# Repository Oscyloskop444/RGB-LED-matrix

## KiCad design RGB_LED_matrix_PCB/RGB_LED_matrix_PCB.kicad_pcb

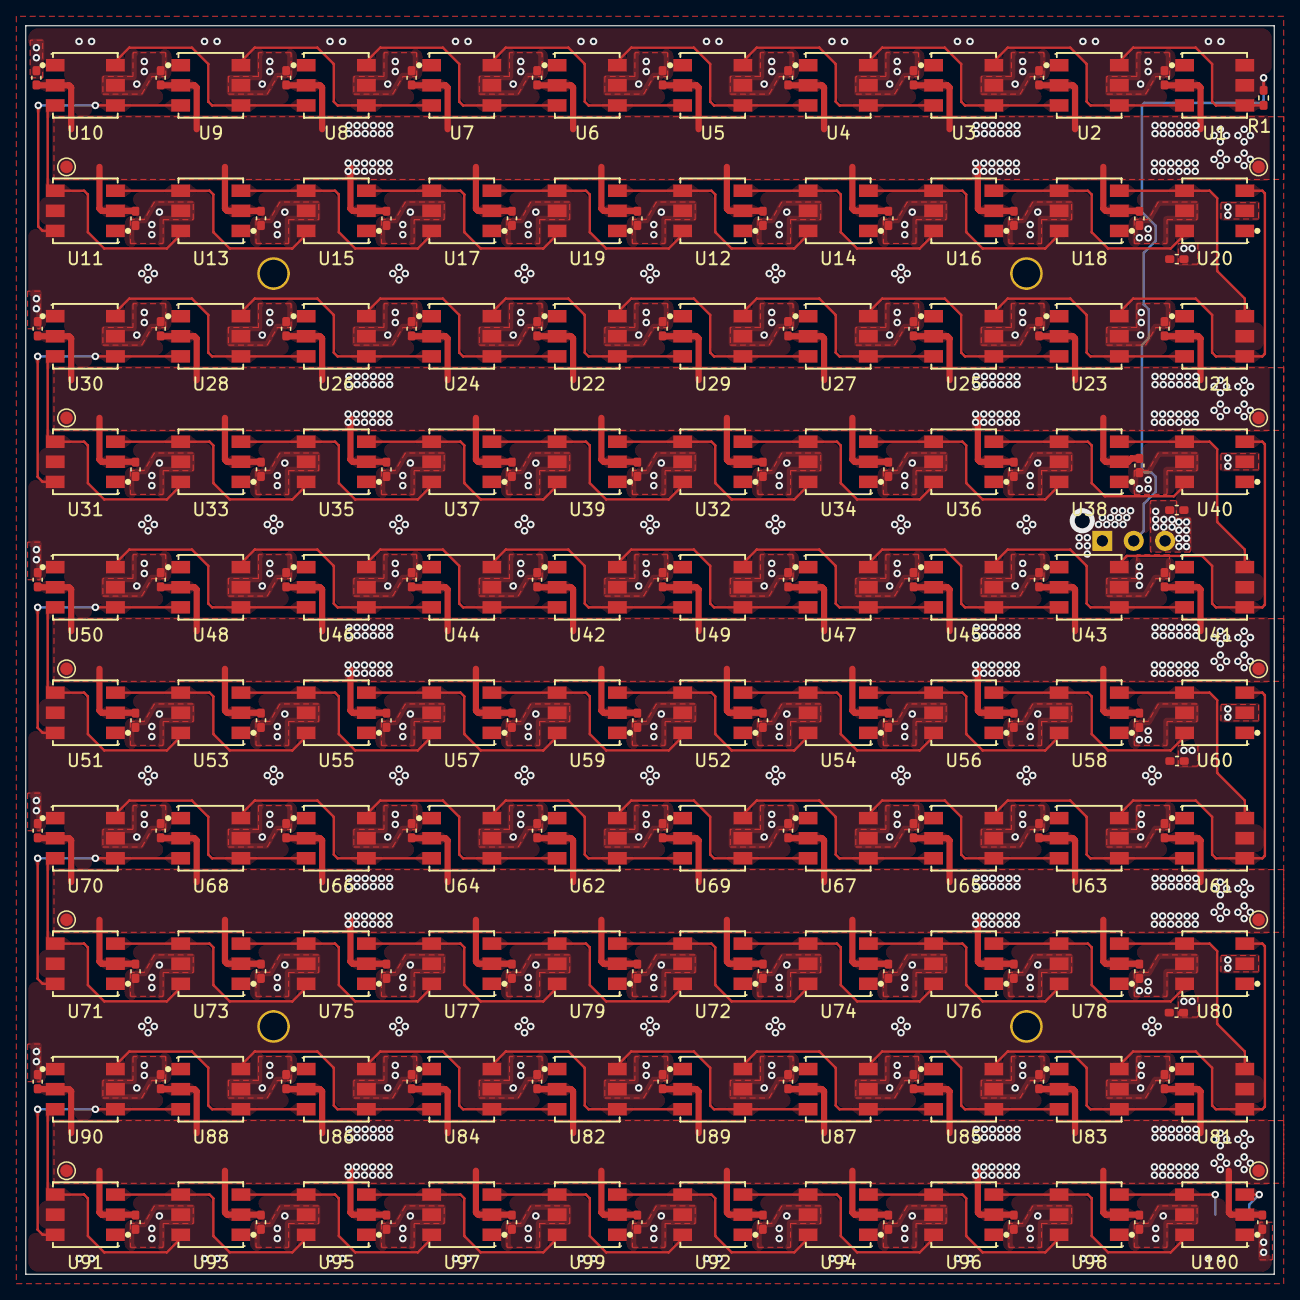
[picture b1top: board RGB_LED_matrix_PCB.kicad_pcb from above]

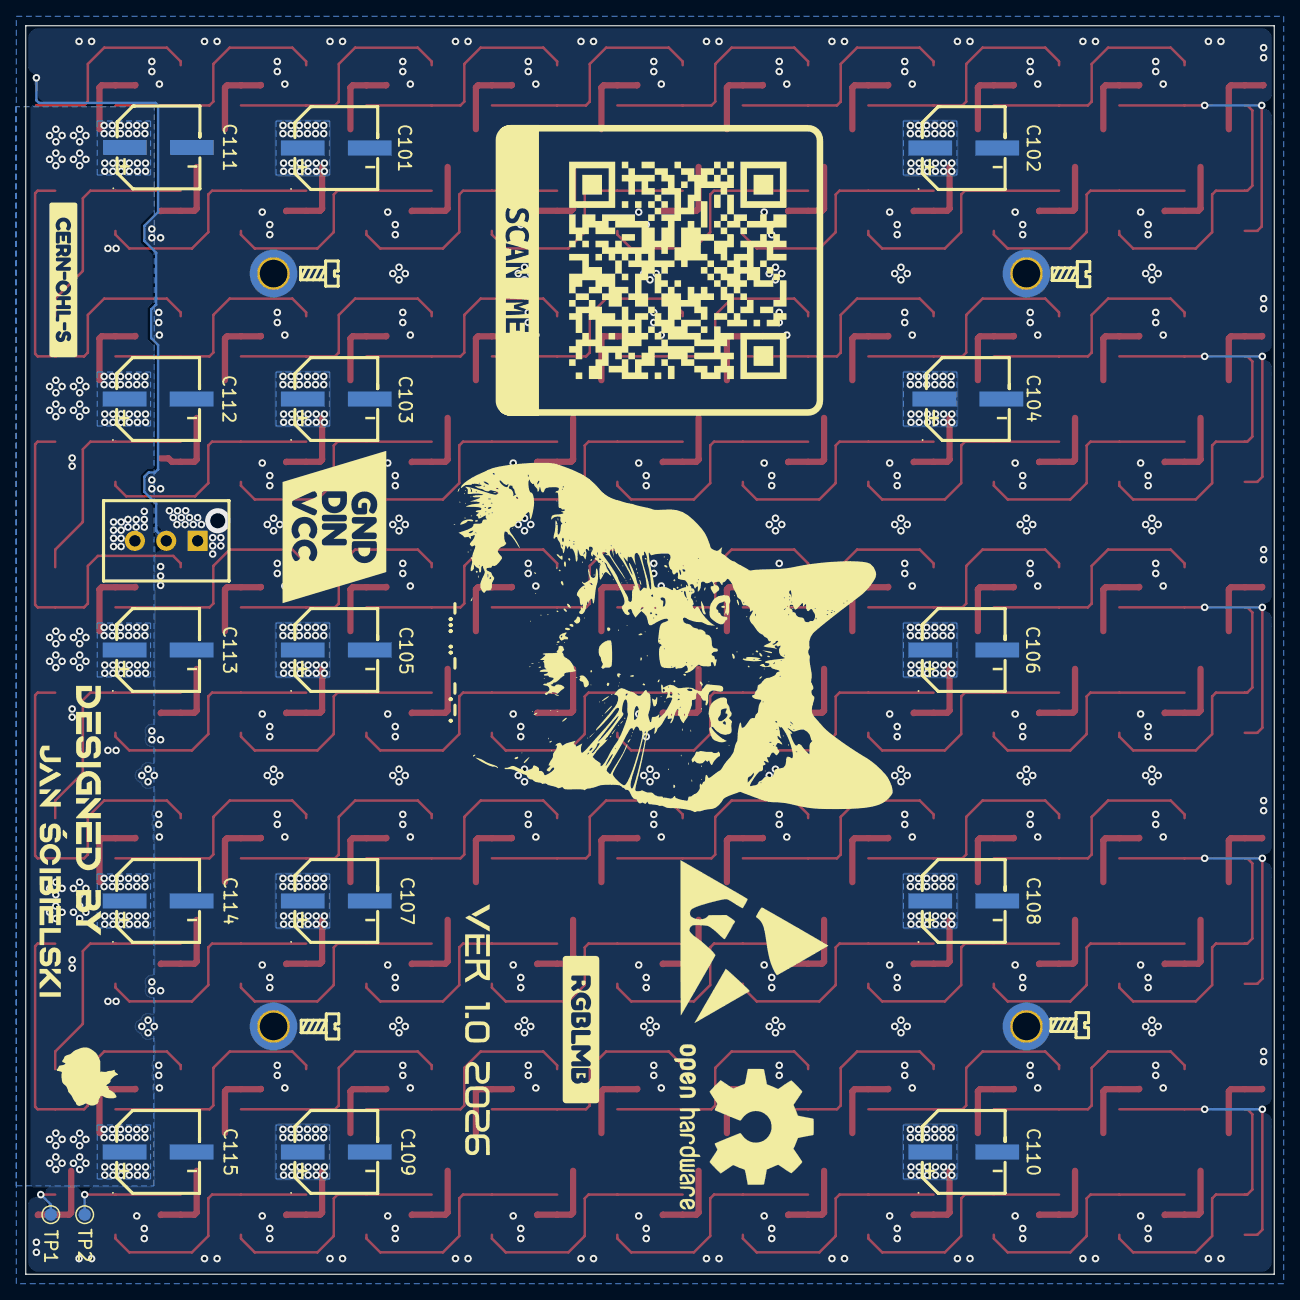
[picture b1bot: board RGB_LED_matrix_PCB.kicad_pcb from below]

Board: 2 copper layers, 99.5 x 99.5 mm, 237 parts (26 on the bottom side), 104 nets.

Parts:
C1, C2, C3, C4, C5, C6, C7, C8, C9, C10, C11, C12, C13, C14, C15, C16, C17, C18, C19, C20, C21, C22, C23, C24, C25, C26, C27, C28, C29, C30, C31, C32, C33, C34, C35, C36, C37, C38, C39, C40, C41, C42, C43, C44, C45, C46, C47, C48, C49, C50, C51, C52, C53, C54, C55, C56, C57, C58, C59, C60, C61, C62, C63, C64, C65, C66, C67, C68, C69, C70, C71, C72, C73, C74, C75, C76, C77, C78, C79, C80, C81, C82, C83, C84, C85, C86, C87, C88, C89, C90, C91, C92, C93, C94, C95, C96, C97, C98, C99, C100: 100nF; C_0402_1005Metric_Pad0.74x0.62mm_HandSolder
C101, C102, C103, C104, C105, C106, C107, C108, C109, C110, C111, C112, C113, C114, C115: 100uF; C19673858_CAP-SMD_BD6_3-L6_5-W6_5-LS7_2-FD_1
CN1: B03B-XASK-1-A(LF)(SN); C264992_CONN-TH_B03B-XASK-1-A-LF-SN
H1, H2, H3, H4: MountingHole_Pad; MountingHole_2.2mm_M2_DIN965_Pad_TopOnly
R1: 470R; R_0402_1005Metric_Pad0.72x0.64mm_HandSolder
TP1: DOUT; TestPoint_Pad_D1.0mm
TP2: DOUT_B; TestPoint_Pad_D1.0mm
TP3, TP4, TP5, TP6, TP7, TP8, TP9, TP10, TP11, TP12: +12V; TestPoint_Pad_D1.0mm
U1, U2, U3, U4, U5, U6, U7, U8, U9, U10, U11, U12, U13, U14, U15, U16, U17, U18, U19, U20, U21, U22, U23, U24, U25, U26, U27, U28, U29, U30, U31, U32, U33, U34, U35, U36, U37, U38, U39, U40, U41, U42, U43, U44, U45, U46, U47, U48, U49, U50, U51, U52, U53, U54, U55, U56, U57, U58, U59, U60, U61, U62, U63, U64, U65, U66, U67, U68, U69, U70, U71, U72, U73, U74, U75, U76, U77, U78, U79, U80, U81, U82, U83, U84, U85, U86, U87, U88, U89, U90, U91, U92, U93, U94, U95, U96, U97, U98, U99, U100: WS2815F; C22371533_LED-SMD_6P-L5_0-W5_0-TL
kibuzzard-6AA54A1E: G***; kibuzzard-6AA54A1E
kobee-studio-6AA9F6C4: Kobee Studio; kobee-studio-6AA9F6C4
kobee-studio-6AA9F9DB: Kobee Studio; kobee-studio-6AA9F9DB
kobee-studio-6AA92370: Kobee Studio; kobee-studio-6AA92370

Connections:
+12V: C1.2, C2.2, C3.2, C4.2, C5.2, C6.2, C7.2, C8.2, C9.2, C10.2, C11.2, C12.2, C13.2, C14.2, C15.2, C16.2, C17.2, C18.2, C19.2, C20.2, C21.2, C22.2, C23.2, C24.2, C25.2, C26.2, C27.2, C28.2, C29.2, C30.2, C31.2, C32.2, C33.2, C34.2, C35.2, C36.2, C37.2, C38.2, C39.2, C40.2, C41.2, C42.2, C43.2, C44.2, C45.2, C46.2, C47.2, C48.2, C49.2, C50.2, C51.2, C52.2, C53.2, C54.2, C55.2, C56.2, C57.2, C58.2, C59.2, C60.2, C61.2, C62.2, C63.2, C64.2, C65.2, C66.2, C67.2, C68.2, C69.2, C70.2, C71.2, C72.2, C73.2, C74.2, C75.2, C76.2, C77.2, C78.2, C79.2, C80.2, C81.2, C82.2, C83.2, C84.2, C85.2, C86.2, C87.2, C88.2, C89.2, C90.2, C91.2, C92.2, C93.2, C94.2, C95.2, C96.2, C97.2, C98.2, C99.2, C100.2, C101.1, C102.1, C103.1, C104.1, C105.1, C106.1, C107.1, C108.1, C109.1, C110.1, C111.1, C112.1, C113.1, C114.1, C115.1, CN1.3, TP3.1 (1_1), TP4.1 (1_1), TP5.1 (1_1), TP6.1 (1_1), TP7.1 (1_1), TP8.1 (1_1), TP9.1 (1_1), TP10.1 (1_1), TP11.1 (1_1), TP12.1 (1_1), U1.2 (VDD), U2.2 (VDD), U3.2 (VDD), U4.2 (VDD), U5.2 (VDD), U6.2 (VDD), U7.2 (VDD), U8.2 (VDD), U9.2 (VDD), U10.2 (VDD), U11.2 (VDD), U12.2 (VDD), U13.2 (VDD), U14.2 (VDD), U15.2 (VDD), U16.2 (VDD), U17.2 (VDD), U18.2 (VDD), U19.2 (VDD), U20.2 (VDD), U21.2 (VDD), U22.2 (VDD), U23.2 (VDD), U24.2 (VDD), U25.2 (VDD), U26.2 (VDD), U27.2 (VDD), U28.2 (VDD), U29.2 (VDD), U30.2 (VDD), U31.2 (VDD), U32.2 (VDD), U33.2 (VDD), U34.2 (VDD), U35.2 (VDD), U36.2 (VDD), U37.2 (VDD), U38.2 (VDD), U39.2 (VDD), U40.2 (VDD), U41.2 (VDD), U42.2 (VDD), U43.2 (VDD), U44.2 (VDD), U45.2 (VDD), U46.2 (VDD), U47.2 (VDD), U48.2 (VDD), U49.2 (VDD), U50.2 (VDD), U51.2 (VDD), U52.2 (VDD), U53.2 (VDD), U54.2 (VDD), U55.2 (VDD), U56.2 (VDD), U57.2 (VDD), U58.2 (VDD), U59.2 (VDD), U60.2 (VDD), U61.2 (VDD), U62.2 (VDD), U63.2 (VDD), U64.2 (VDD), U65.2 (VDD), U66.2 (VDD), U67.2 (VDD), U68.2 (VDD), U69.2 (VDD), U70.2 (VDD), U71.2 (VDD), U72.2 (VDD), U73.2 (VDD), U74.2 (VDD), U75.2 (VDD), U76.2 (VDD), U77.2 (VDD), U78.2 (VDD), U79.2 (VDD), U80.2 (VDD), U81.2 (VDD), U82.2 (VDD), U83.2 (VDD), U84.2 (VDD), U85.2 (VDD), U86.2 (VDD), U87.2 (VDD), U88.2 (VDD), U89.2 (VDD), U90.2 (VDD), U91.2 (VDD), U92.2 (VDD), U93.2 (VDD), U94.2 (VDD), U95.2 (VDD), U96.2 (VDD), U97.2 (VDD), U98.2 (VDD), U99.2 (VDD), U100.2 (VDD)
/LED_ROW1/DOUT1: U20.3 (DO), U21.4 (DIN1), U23.6 (DIN2)
/LED_ROW1/DOUT2: U18.3 (DO), U20.4 (DIN1), U21.6 (DIN2)
/LED_ROW2/DOUT1: U30.3 (DO), U31.4 (DIN1), U33.6 (DIN2)
/LED_ROW2/DOUT2: U28.3 (DO), U30.4 (DIN1), U31.6 (DIN2)
/LED_ROW3/DOUT1: U40.3 (DO), U41.4 (DIN1), U43.6 (DIN2)
/LED_ROW3/DOUT2: U38.3 (DO), U40.4 (DIN1), U41.6 (DIN2)
/LED_ROW4/DOUT1: U50.3 (DO), U51.4 (DIN1), U53.6 (DIN2)
/LED_ROW4/DOUT2: U48.3 (DO), U50.4 (DIN1), U51.6 (DIN2)
/LED_ROW5/DOUT1: U60.3 (DO), U61.4 (DIN1), U63.6 (DIN2)
/LED_ROW5/DOUT2: U58.3 (DO), U60.4 (DIN1), U61.6 (DIN2)
/LED_ROW6/DOUT1: U70.3 (DO), U71.4 (DIN1), U73.6 (DIN2)
/LED_ROW6/DOUT2: U68.3 (DO), U70.4 (DIN1), U71.6 (DIN2)
/LED_ROW7/DOUT1: U80.3 (DO), U81.4 (DIN1), U83.6 (DIN2)
/LED_ROW7/DOUT2: U78.3 (DO), U80.4 (DIN1), U81.6 (DIN2)
/LED_ROW8/DOUT1: U90.3 (DO), U91.4 (DIN1), U93.6 (DIN2)
/LED_ROW8/DOUT2: U88.3 (DO), U90.4 (DIN1), U91.6 (DIN2)
/LED_ROW9/DOUT1: TP1.1 (1_1), U100.3 (DO)
/LED_ROW9/DOUT2: TP2.1 (1_1), U98.3 (DO), U100.4 (DIN1)
/LED_ROW/DIN1: R1.1, U1.4 (DIN1), U2.6 (DIN2)
/LED_ROW/DOUT1: U10.3 (DO), U11.4 (DIN1), U13.6 (DIN2)
/LED_ROW/DOUT2: U9.3 (DO), U10.4 (DIN1), U11.6 (DIN2)
GND: C1.1, C2.1, C3.1, C4.1, C5.1, C6.1, C7.1, C8.1, C9.1, C10.1, C11.1, C12.1, C13.1, C14.1, C15.1, C16.1, C17.1, C18.1, C19.1, C20.1, C21.1, C22.1, C23.1, C24.1, C25.1, C26.1, C27.1, C28.1, C29.1, C30.1, C31.1, C32.1, C33.1, C34.1, C35.1, C36.1, C37.1, C38.1, C39.1, C40.1, C41.1, C42.1, C43.1, C44.1, C45.1, C46.1, C47.1, C48.1, C49.1, C50.1, C51.1, C52.1, C53.1, C54.1, C55.1, C56.1, C57.1, C58.1, C59.1, C60.1, C61.1, C62.1, C63.1, C64.1, C65.1, C66.1, C67.1, C68.1, C69.1, C70.1, C71.1, C72.1, C73.1, C74.1, C75.1, C76.1, C77.1, C78.1, C79.1, C80.1, C81.1, C82.1, C83.1, C84.1, C85.1, C86.1, C87.1, C88.1, C89.1, C90.1, C91.1, C92.1, C93.1, C94.1, C95.1, C96.1, C97.1, C98.1, C99.1, C100.1, C101.2, C102.2, C103.2, C104.2, C105.2, C106.2, C107.2, C108.2, C109.2, C110.2, C111.2, C112.2, C113.2, C114.2, C115.2, CN1.1, H1.1 (1_1), H2.1 (1_1), H3.1 (1_1), H4.1 (1_1), U1.5 (GND), U1.6 (DIN2), U2.5 (GND), U3.5 (GND), U4.5 (GND), U5.5 (GND), U6.5 (GND), U7.5 (GND), U8.5 (GND), U9.5 (GND), U10.5 (GND), U11.5 (GND), U12.5 (GND), U13.5 (GND), U14.5 (GND), U15.5 (GND), U16.5 (GND), U17.5 (GND), U18.5 (GND), U19.5 (GND), U20.5 (GND), U21.5 (GND), U22.5 (GND), U23.5 (GND), U24.5 (GND), U25.5 (GND), U26.5 (GND), U27.5 (GND), U28.5 (GND), U29.5 (GND), U30.5 (GND), U31.5 (GND), U32.5 (GND), U33.5 (GND), U34.5 (GND), U35.5 (GND), U36.5 (GND), U37.5 (GND), U38.5 (GND), U39.5 (GND), U40.5 (GND), U41.5 (GND), U42.5 (GND), U43.5 (GND), U44.5 (GND), U45.5 (GND), U46.5 (GND), U47.5 (GND), U48.5 (GND), U49.5 (GND), U50.5 (GND), U51.5 (GND), U52.5 (GND), U53.5 (GND), U54.5 (GND), U55.5 (GND), U56.5 (GND), U57.5 (GND), U58.5 (GND), U59.5 (GND), U60.5 (GND), U61.5 (GND), U62.5 (GND), U63.5 (GND), U64.5 (GND), U65.5 (GND), U66.5 (GND), U67.5 (GND), U68.5 (GND), U69.5 (GND), U70.5 (GND), U71.5 (GND), U72.5 (GND), U73.5 (GND), U74.5 (GND), U75.5 (GND), U76.5 (GND), U77.5 (GND), U78.5 (GND), U79.5 (GND), U80.5 (GND), U81.5 (GND), U82.5 (GND), U83.5 (GND), U84.5 (GND), U85.5 (GND), U86.5 (GND), U87.5 (GND), U88.5 (GND), U89.5 (GND), U90.5 (GND), U91.5 (GND), U92.5 (GND), U93.5 (GND), U94.5 (GND), U95.5 (GND), U96.5 (GND), U97.5 (GND), U98.5 (GND), U99.5 (GND), U100.5 (GND)
unnamed: CN1.2, R1.2
unnamed: U1.3 (DO), U2.4 (DIN1), U3.6 (DIN2)
unnamed: U2.3 (DO), U3.4 (DIN1), U4.6 (DIN2)
unnamed: U3.3 (DO), U4.4 (DIN1), U5.6 (DIN2)
unnamed: U4.3 (DO), U5.4 (DIN1), U6.6 (DIN2)
unnamed: U5.3 (DO), U6.4 (DIN1), U7.6 (DIN2)
unnamed: U6.3 (DO), U7.4 (DIN1), U8.6 (DIN2)
unnamed: U7.3 (DO), U8.4 (DIN1), U9.6 (DIN2)
unnamed: U8.3 (DO), U9.4 (DIN1), U10.6 (DIN2)
unnamed: U11.3 (DO), U13.4 (DIN1), U15.6 (DIN2)
unnamed: U12.4 (DIN1), U14.6 (DIN2), U19.3 (DO)
unnamed: U12.6 (DIN2), U17.3 (DO), U19.4 (DIN1)
unnamed: U12.3 (DO), U14.4 (DIN1), U16.6 (DIN2)
unnamed: U13.3 (DO), U15.4 (DIN1), U17.6 (DIN2)
unnamed: U14.3 (DO), U16.4 (DIN1), U18.6 (DIN2)
unnamed: U15.3 (DO), U17.4 (DIN1), U19.6 (DIN2)
unnamed: U16.3 (DO), U18.4 (DIN1), U20.6 (DIN2)
unnamed: U21.3 (DO), U23.4 (DIN1), U25.6 (DIN2)
unnamed: U22.4 (DIN1), U24.6 (DIN2), U29.3 (DO)
unnamed: U22.6 (DIN2), U27.3 (DO), U29.4 (DIN1)
unnamed: U22.3 (DO), U24.4 (DIN1), U26.6 (DIN2)
unnamed: U23.3 (DO), U25.4 (DIN1), U27.6 (DIN2)
unnamed: U24.3 (DO), U26.4 (DIN1), U28.6 (DIN2)
unnamed: U25.3 (DO), U27.4 (DIN1), U29.6 (DIN2)
unnamed: U26.3 (DO), U28.4 (DIN1), U30.6 (DIN2)
unnamed: U31.3 (DO), U33.4 (DIN1), U35.6 (DIN2)
unnamed: U32.4 (DIN1), U34.6 (DIN2), U39.3 (DO)
unnamed: U32.6 (DIN2), U37.3 (DO), U39.4 (DIN1)
unnamed: U32.3 (DO), U34.4 (DIN1), U36.6 (DIN2)
unnamed: U33.3 (DO), U35.4 (DIN1), U37.6 (DIN2)
unnamed: U34.3 (DO), U36.4 (DIN1), U38.6 (DIN2)
unnamed: U35.3 (DO), U37.4 (DIN1), U39.6 (DIN2)
unnamed: U36.3 (DO), U38.4 (DIN1), U40.6 (DIN2)
unnamed: U41.3 (DO), U43.4 (DIN1), U45.6 (DIN2)
unnamed: U42.4 (DIN1), U44.6 (DIN2), U49.3 (DO)
unnamed: U42.6 (DIN2), U47.3 (DO), U49.4 (DIN1)
unnamed: U42.3 (DO), U44.4 (DIN1), U46.6 (DIN2)
unnamed: U43.3 (DO), U45.4 (DIN1), U47.6 (DIN2)
unnamed: U44.3 (DO), U46.4 (DIN1), U48.6 (DIN2)
unnamed: U45.3 (DO), U47.4 (DIN1), U49.6 (DIN2)
unnamed: U46.3 (DO), U48.4 (DIN1), U50.6 (DIN2)
unnamed: U51.3 (DO), U53.4 (DIN1), U55.6 (DIN2)
unnamed: U52.4 (DIN1), U54.6 (DIN2), U59.3 (DO)
unnamed: U52.6 (DIN2), U57.3 (DO), U59.4 (DIN1)
unnamed: U52.3 (DO), U54.4 (DIN1), U56.6 (DIN2)
unnamed: U53.3 (DO), U55.4 (DIN1), U57.6 (DIN2)
unnamed: U54.3 (DO), U56.4 (DIN1), U58.6 (DIN2)
unnamed: U55.3 (DO), U57.4 (DIN1), U59.6 (DIN2)
unnamed: U56.3 (DO), U58.4 (DIN1), U60.6 (DIN2)
unnamed: U61.3 (DO), U63.4 (DIN1), U65.6 (DIN2)
unnamed: U62.4 (DIN1), U64.6 (DIN2), U69.3 (DO)
unnamed: U62.6 (DIN2), U67.3 (DO), U69.4 (DIN1)
unnamed: U62.3 (DO), U64.4 (DIN1), U66.6 (DIN2)
unnamed: U63.3 (DO), U65.4 (DIN1), U67.6 (DIN2)
unnamed: U64.3 (DO), U66.4 (DIN1), U68.6 (DIN2)
unnamed: U65.3 (DO), U67.4 (DIN1), U69.6 (DIN2)
unnamed: U66.3 (DO), U68.4 (DIN1), U70.6 (DIN2)
unnamed: U71.3 (DO), U73.4 (DIN1), U75.6 (DIN2)
unnamed: U72.4 (DIN1), U74.6 (DIN2), U79.3 (DO)
unnamed: U72.6 (DIN2), U77.3 (DO), U79.4 (DIN1)
unnamed: U72.3 (DO), U74.4 (DIN1), U76.6 (DIN2)
unnamed: U73.3 (DO), U75.4 (DIN1), U77.6 (DIN2)
unnamed: U74.3 (DO), U76.4 (DIN1), U78.6 (DIN2)
unnamed: U75.3 (DO), U77.4 (DIN1), U79.6 (DIN2)
unnamed: U76.3 (DO), U78.4 (DIN1), U80.6 (DIN2)
unnamed: U81.3 (DO), U83.4 (DIN1), U85.6 (DIN2)
unnamed: U82.4 (DIN1), U84.6 (DIN2), U89.3 (DO)
unnamed: U82.6 (DIN2), U87.3 (DO), U89.4 (DIN1)
unnamed: U82.3 (DO), U84.4 (DIN1), U86.6 (DIN2)
unnamed: U83.3 (DO), U85.4 (DIN1), U87.6 (DIN2)
unnamed: U84.3 (DO), U86.4 (DIN1), U88.6 (DIN2)
unnamed: U85.3 (DO), U87.4 (DIN1), U89.6 (DIN2)
unnamed: U86.3 (DO), U88.4 (DIN1), U90.6 (DIN2)
unnamed: U91.3 (DO), U93.4 (DIN1), U95.6 (DIN2)
unnamed: U92.4 (DIN1), U94.6 (DIN2), U99.3 (DO)
unnamed: U92.6 (DIN2), U97.3 (DO), U99.4 (DIN1)
unnamed: U92.3 (DO), U94.4 (DIN1), U96.6 (DIN2)
unnamed: U93.3 (DO), U95.4 (DIN1), U97.6 (DIN2)
unnamed: U94.3 (DO), U96.4 (DIN1), U98.6 (DIN2)
unnamed: U95.3 (DO), U97.4 (DIN1), U99.6 (DIN2)
unnamed: U96.3 (DO), U98.4 (DIN1), U100.6 (DIN2)

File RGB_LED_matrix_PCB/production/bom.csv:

Designator,Footprint,Quantity,Value,LCSC Part #
"C1, C10, C100, C11, C12, C13, C14, C15, C16, C17, C18, C19, C2, C20, C21, C22, C23, C24, C25, C26, C27, C28, C29, C3, C30, C31, C32, C33, C34, C35, C36, C37, C38, C39, C4, C40, C41, C42, C43, C44, C45, C46, C47, C48, C49, C5, C50, C51, C52, C53, C54, C55, C56, C57, C58, C59, C6, C60, C61, C62, C63, C64, C65, C66, C67, C68, C69, C7, C70, C71, C72, C73, C74, C75, C76, C77, C78, C79, C8, C80, C81, C82, C83, C84, C85, C86, C87, C88, C89, C9, C90, C91, C92, C93, C94, C95, C96, C97, C98, C99",0402,100,100nF,
"C101, C102, C103, C104, C105, C106, C107, C108, C109, C110, C111, C112, C113, C114, C115",C19673858_CAP-SMD_BD6_3-L6_5-W6_5-LS7_2-FD_1,15,100uF,C19673858
CN1,C264992_CONN-TH_B03B-XASK-1-A-LF-SN,1,B03B-XASK-1-A(LF)(SN),C264992
R1,0402,1,470R,
TP1,TestPoint_Pad_D1.0mm,1,DOUT,
"TP10, TP11, TP12, TP3, TP4, TP5, TP6, TP7, TP8, TP9",TestPoint_Pad_D1.0mm,10,+12V,
TP2,TestPoint_Pad_D1.0mm,1,DOUT_B,
"U1, U10, U100, U11, U12, U13, U14, U15, U16, U17, U18, U19, U2, U20, U21, U22, U23, U24, U25, U26, U27, U28, U29, U3, U30, U31, U32, U33, U34, U35, U36, U37, U38, U39, U4, U40, U41, U42, U43, U44, U45, U46, U47, U48, U49, U5, U50, U51, U52, U53, U54, U55, U56, U57, U58, U59, U6, U60, U61, U62, U63, U64, U65, U66, U67, U68, U69, U7, U70, U71, U72, U73, U74, U75, U76, U77, U78, U79, U8, U80, U81, U82, U83, U84, U85, U86, U87, U88, U89, U9, U90, U91, U92, U93, U94, U95, U96, U97, U98, U99",C22371533_LED-SMD_6P-L5_0-W5_0-TL,100,WS2815F,C22371533

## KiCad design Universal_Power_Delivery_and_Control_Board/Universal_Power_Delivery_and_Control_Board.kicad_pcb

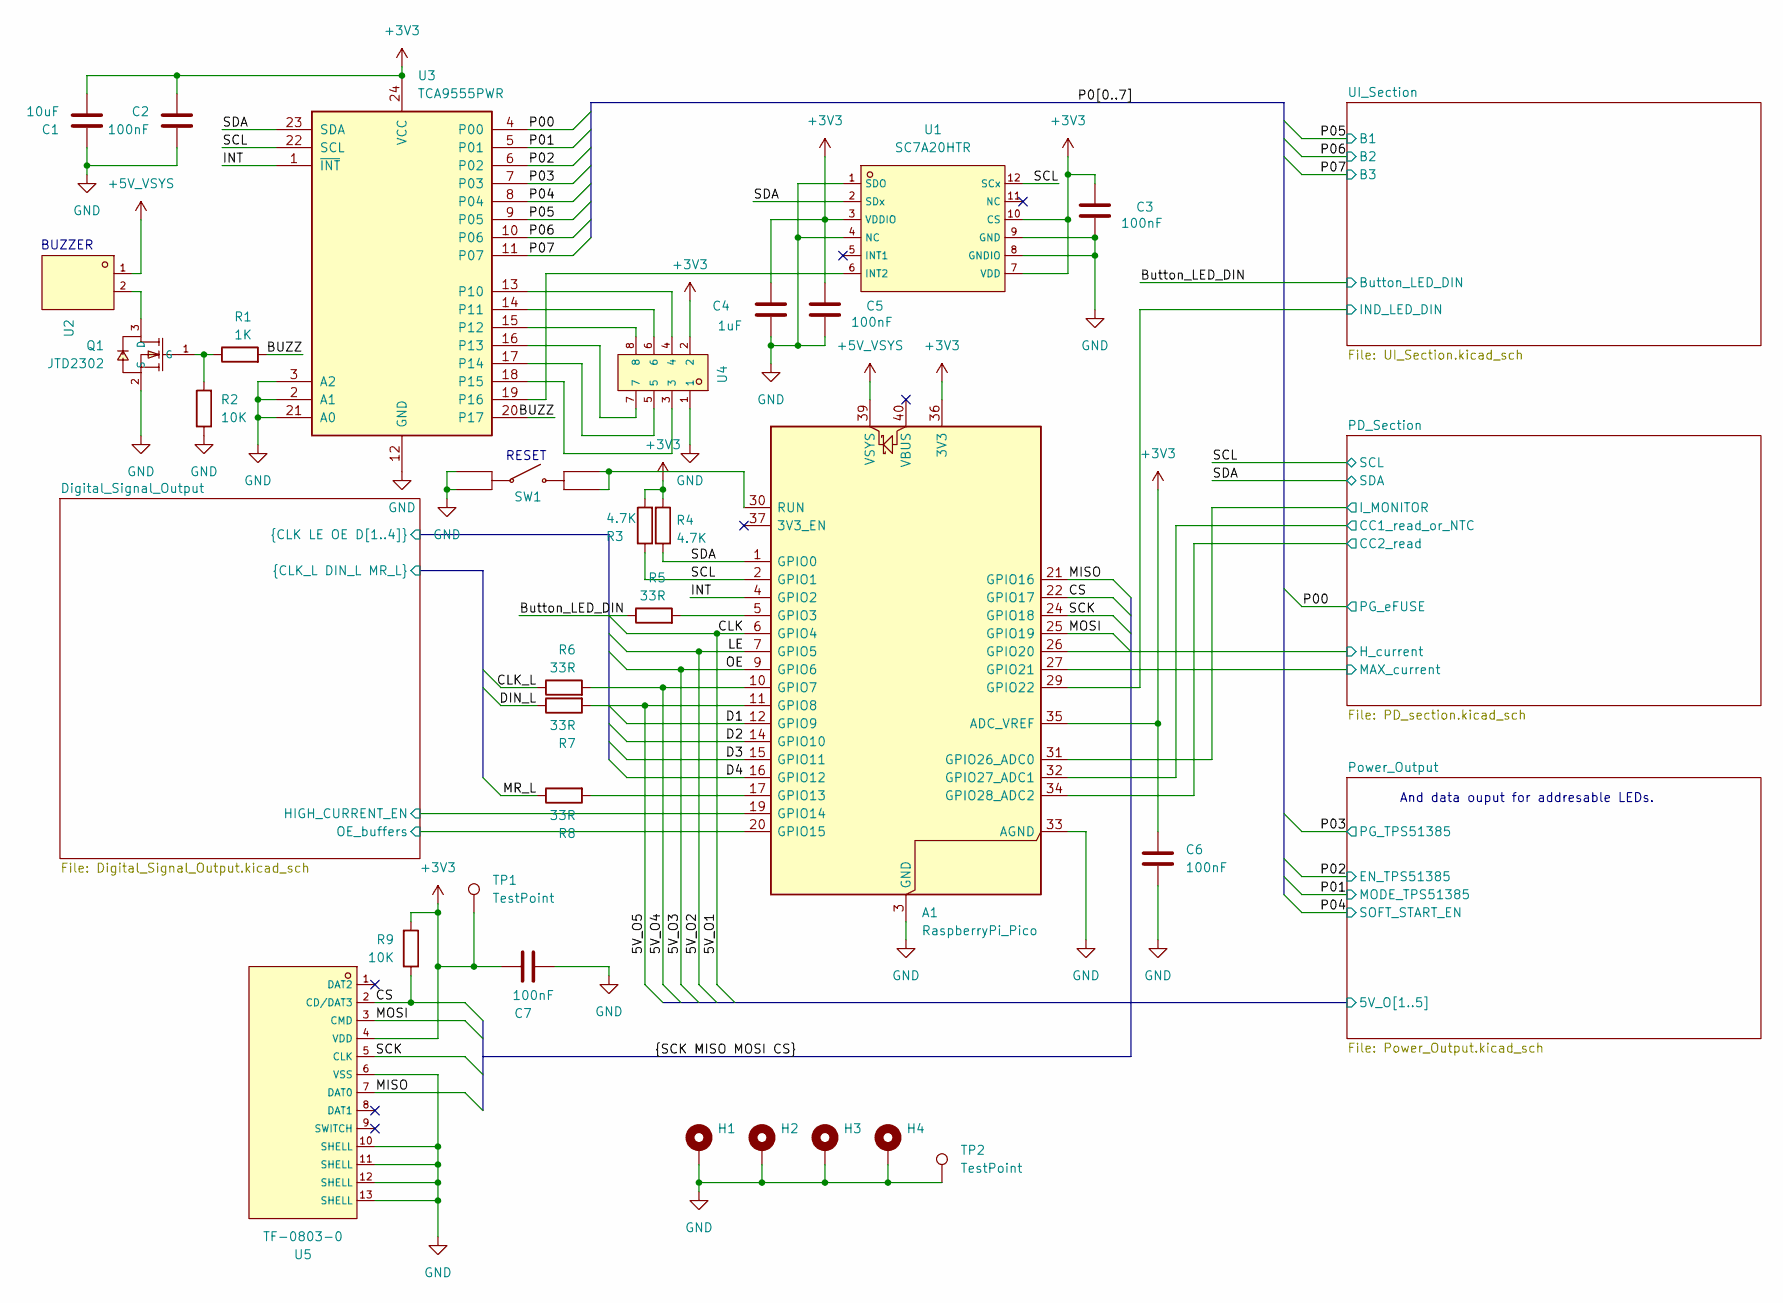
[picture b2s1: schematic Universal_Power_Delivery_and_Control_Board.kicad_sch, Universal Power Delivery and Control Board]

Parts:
A1: RaspberryPi_Pico; RaspberryPi_Pico_Common_Unspecified
C1: 10uF; C_0805_2012Metric_Pad1.18x1.45mm_HandSolder
C2, C3, C5, C6, C7: 100nF; C_0402_1005Metric_Pad0.74x0.62mm_HandSolder
C4: 1uF; C_0402_1005Metric_Pad0.74x0.62mm_HandSolder
H1, H2, H3, H4: MountingHole_Pad; MountingHole_2.2mm_M2_Pad_Via
Q1: JTD2302; C42443455_SOT-23-3_L2_9-W1_5-P2_0-LS2_5-BR; LCSC C42443455
R1: 1K; R_0402_1005Metric_Pad0.72x0.64mm_HandSolder
R2, R9: 10K; R_0402_1005Metric_Pad0.72x0.64mm_HandSolder
R3, R4: 4.7K; R_0402_1005Metric_Pad0.72x0.64mm_HandSolder
R5, R6, R7, R8: 33R; R_0402_1005Metric_Pad0.72x0.64mm_HandSolder
SW1: TSA016A2526A; C2888428_SW-SMD_4P-L4_2-W3_3-P2_15-LS4_6; LCSC C2888428
TP1, TP2: TestPoint; TestPoint_Pad_1.5x1.5mm
U1: SC7A20HTR; C19274408_LGA-12_L2_0-W2_0-P0_50-TL; LCSC C19274408
U2: S2B-ZR (LF)(SN); C157930_CONN-TH_S2B-ZR-LF-SN; LCSC C157930
U3: TCA9555PWR; TSSOP-24_4.4x7.8mm_P0.65mm
U4: HC-PM254-8.5H-2X4PW-02A; C42163146_HDR-TH_8P-P2_54-H-F-R2-C4-S2_54-W8_5; LCSC C42163146
U5: TF-0803-0; C5362199_TF-SMD_XKTF-0803-0; LCSC C5362199

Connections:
+3V3: A1.35 (ADC_VREF), A1.36 (3V3), C1.2, C2.1, C3.2, C4.2, C5.2, C6.1, C7.1, R3.2, R4.2, R9.2, TP1.1 (1_1), U1.3 (VDDIO), U1.7 (VDD), U1.10 (CS), U3.24 (VCC), U4.2, U5.4 (VDD); also elsewhere on the board
+5V_VSYS: A1.39 (VSYS), U2.1; also elsewhere on the board
/BUZZ: R1.2, U3.20 (P17)
/Button_LED_DIN: R5.1; also elsewhere on the board
/CS: A1.22 (GPIO17), R9.1, U5.2 (CD/DAT3)
/Digital_Signal_Output/CLK_L: R6.1; also elsewhere on the board
/Digital_Signal_Output/D1: A1.12 (GPIO9); also elsewhere on the board
/Digital_Signal_Output/D2: A1.14 (GPIO10); also elsewhere on the board
/Digital_Signal_Output/D3: A1.15 (GPIO11); also elsewhere on the board
/Digital_Signal_Output/D4: A1.16 (GPIO12); also elsewhere on the board
/Digital_Signal_Output/DIN_L: R7.1; also elsewhere on the board
/Digital_Signal_Output/HIGH_CURRENT_EN: A1.19 (GPIO14); also elsewhere on the board
/Digital_Signal_Output/MR_L: R8.1; also elsewhere on the board
/Digital_Signal_Output/OE_buffers: A1.20 (GPIO15); also elsewhere on the board
/INT: A1.4 (GPIO2), U3.1 (~INT)
/MISO: A1.21 (GPIO16), U5.7 (DAT0)
/MOSI: A1.25 (GPIO19), U5.3 (CMD)
/P00: U3.4 (P00); also elsewhere on the board
/P01: U3.5 (P01); also elsewhere on the board
/P02: U3.6 (P02); also elsewhere on the board
/P03: U3.7 (P03); also elsewhere on the board
/P04: U3.8 (P04); also elsewhere on the board
/P05: U3.9 (P05); also elsewhere on the board
/P06: U3.10 (P06); also elsewhere on the board
/P07: U3.11 (P07); also elsewhere on the board
/PD_Section/CC1_read_or_NTC: A1.32 (GPIO27_ADC1); also elsewhere on the board
/PD_Section/CC2_read: A1.34 (GPIO28_ADC2); also elsewhere on the board
/PD_Section/H_current: A1.26 (GPIO20); also elsewhere on the board
/PD_Section/I_MONITOR: A1.31 (GPIO26_ADC0); also elsewhere on the board
/PD_Section/MAX_current: A1.27 (GPIO21); also elsewhere on the board
/Power_Output/5V_O1: A1.6 (GPIO4); also elsewhere on the board
/Power_Output/5V_O2: A1.7 (GPIO5); also elsewhere on the board
/Power_Output/5V_O3: A1.9 (GPIO6); also elsewhere on the board
/Power_Output/5V_O4: A1.10 (GPIO7), R6.2; also elsewhere on the board
/Power_Output/5V_O5: A1.11 (GPIO8), R7.2; also elsewhere on the board
/SCK: A1.24 (GPIO18), U5.5 (CLK)
/SCL: A1.2 (GPIO1), R3.1, U1.12 (SCx), U3.22 (SCL); also elsewhere on the board
/SDA: A1.1 (GPIO0), R4.1, U1.2 (SDx), U3.23 (SDA); also elsewhere on the board
/UI_Section/IND_LED_DIN: A1.29 (GPIO22); also elsewhere on the board
GND: A1.3 (GND), A1.8 (GND), A1.13 (GND), A1.18 (GND), A1.23 (GND), A1.28 (GND), A1.33 (AGND), A1.38 (GND), C1.1, C2.2, C3.1, C4.1, C5.1, C6.2, C7.2, H1.1 (1_1), H2.1 (1_1), H3.1 (1_1), H4.1 (1_1), Q1.2 (S), R2.1, SW1.1, SW1.2, TP2.1 (1_1), U1.1 (SDO), U1.4 (NC), U1.8 (GNDIO), U1.9 (GND), U3.2 (A1), U3.3 (A2), U3.12 (GND), U3.21 (A0), U4.1, U5.6 (VSS), U5.10 (SHELL), U5.11 (SHELL), U5.12 (SHELL), U5.13 (SHELL); also elsewhere on the board
unnamed: A1.5 (GPIO3), R5.2
unnamed: A1.17 (GPIO13), R8.2
unnamed: A1.30 (RUN), SW1.3, SW1.4
unnamed: Q1.3 (D), U2.2
unnamed: Q1.1 (G), R1.1, R2.2
unnamed: U1.6 (INT2), U3.19 (P16)
unnamed: U3.13 (P10), U4.4
unnamed: U3.14 (P11), U4.6
unnamed: U3.15 (P12), U4.8
unnamed: U3.16 (P13), U4.7
unnamed: U3.17 (P14), U4.5
unnamed: U3.18 (P15), U4.3

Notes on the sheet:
RESET
BUZZER
And data ouput for addresable LEDs.

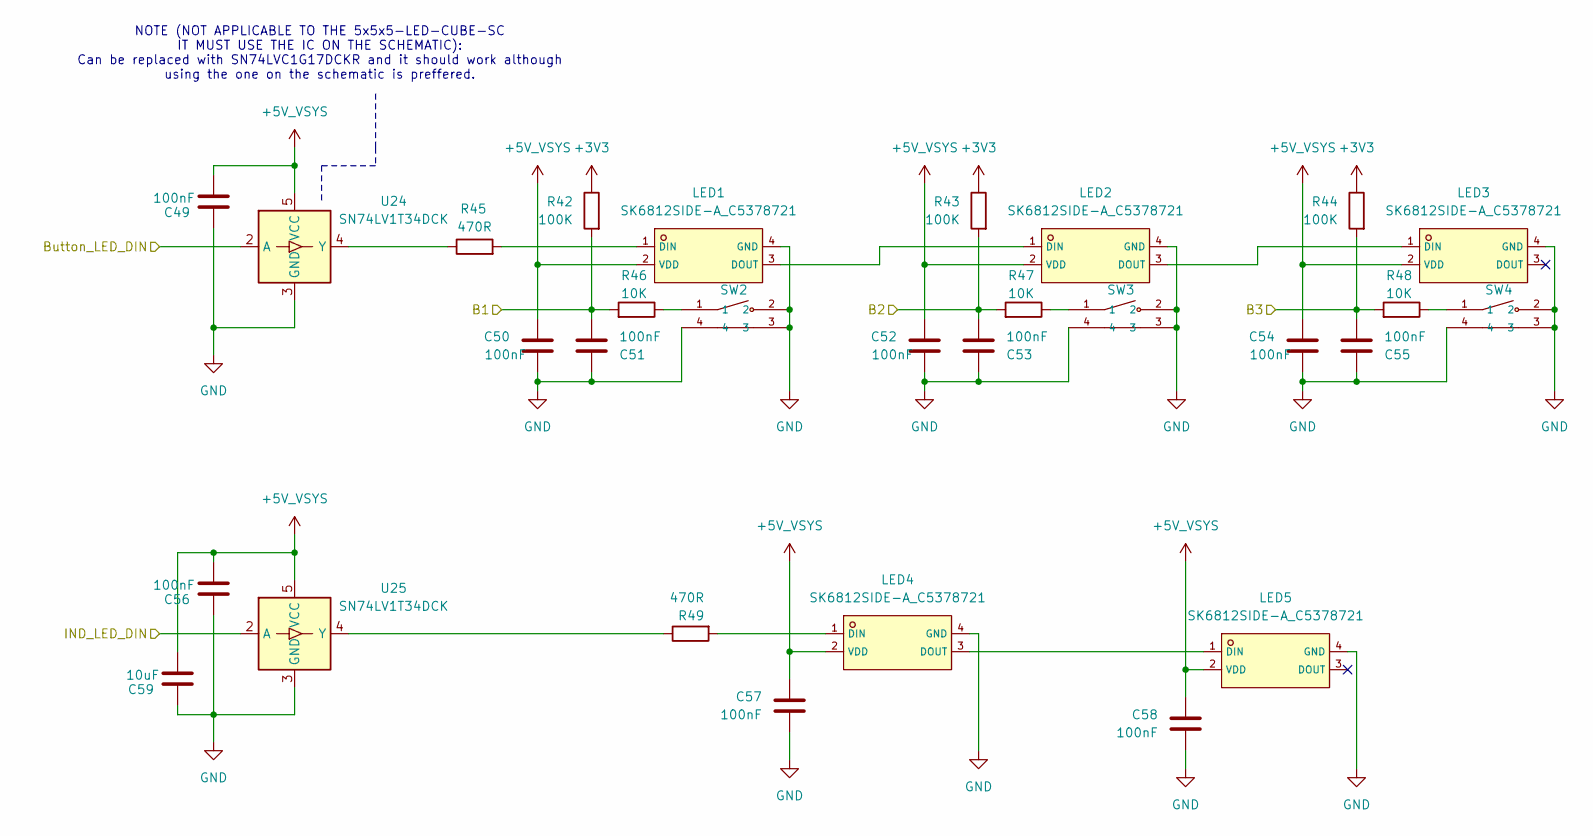
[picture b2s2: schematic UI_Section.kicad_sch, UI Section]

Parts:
C49, C50, C51, C52, C53, C54, C55, C56, C57, C58: 100nF; C_0402_1005Metric_Pad0.74x0.62mm_HandSolder
C59: 10uF; C_0805_2012Metric_Pad1.18x1.45mm_HandSolder
LED1, LED2, LED3, LED4, LED5: SK6812SIDE-A_C5378721; C5378721_LED-SMD_4P-L4_0-W1_6-L; LCSC C5378721
R42, R43, R44: 100K; R_0402_1005Metric_Pad0.72x0.64mm_HandSolder
R45, R49: 470R; R_0402_1005Metric_Pad0.72x0.64mm_HandSolder
R46, R47, R48: 10K; R_0402_1005Metric_Pad0.72x0.64mm_HandSolder
SW2, SW3, SW4: TS1102-TD35HBM; C36936640_SW-SMD_TS1102-TD35HBM; LCSC C36936640
U24, U25: SN74LV1T34DCK; SOT-353_SC-70-5

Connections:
+3V3: R42.1, R43.1, R44.1; also elsewhere on the board
+5V_VSYS: C49.1, C50.1, C52.1, C54.1, C56.1, C57.1, C58.1, C59.1, LED1.2 (VDD), LED2.2 (VDD), LED3.2 (VDD), LED4.2 (VDD), LED5.2 (VDD), U24.5 (VCC), U25.5 (VCC); also elsewhere on the board
/Button_LED_DIN: U24.2 (A); also elsewhere on the board
/P05: C51.2, R42.2, R46.2; also elsewhere on the board
/P06: C53.2, R43.2, R47.2; also elsewhere on the board
/P07: C55.2, R44.2, R48.2; also elsewhere on the board
/UI_Section/IND_LED_DIN: U25.2 (A); also elsewhere on the board
GND: C49.2, C50.2, C51.1, C52.2, C53.1, C54.2, C55.1, C56.2, C57.2, C58.2, C59.2, LED1.4 (GND), LED2.4 (GND), LED3.4 (GND), LED4.4 (GND), LED5.4 (GND), SW2.2, SW2.3, SW2.4, SW3.2, SW3.3, SW3.4, SW4.2, SW4.3, SW4.4, U24.3 (GND), U25.3 (GND); also elsewhere on the board
unnamed: LED1.1 (DIN), R45.2
unnamed: LED1.3 (DOUT), LED2.1 (DIN)
unnamed: LED2.3 (DOUT), LED3.1 (DIN)
unnamed: LED4.1 (DIN), R49.2
unnamed: LED4.3 (DOUT), LED5.1 (DIN)
unnamed: R46.1, SW2.1
unnamed: R47.1, SW3.1
unnamed: R48.1, SW4.1
unnamed: R45.1, U24.4 (Y)
unnamed: R49.1, U25.4 (Y)

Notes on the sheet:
NOTE (NOT APPLICABLE TO THE 5x5x5-LED-CUBE-SC IT MUST USE THE IC ON THE SCHEMATIC): Can be replaced with SN74LVC1G17DCKR and it should work although using the one on the schematic is preffered.

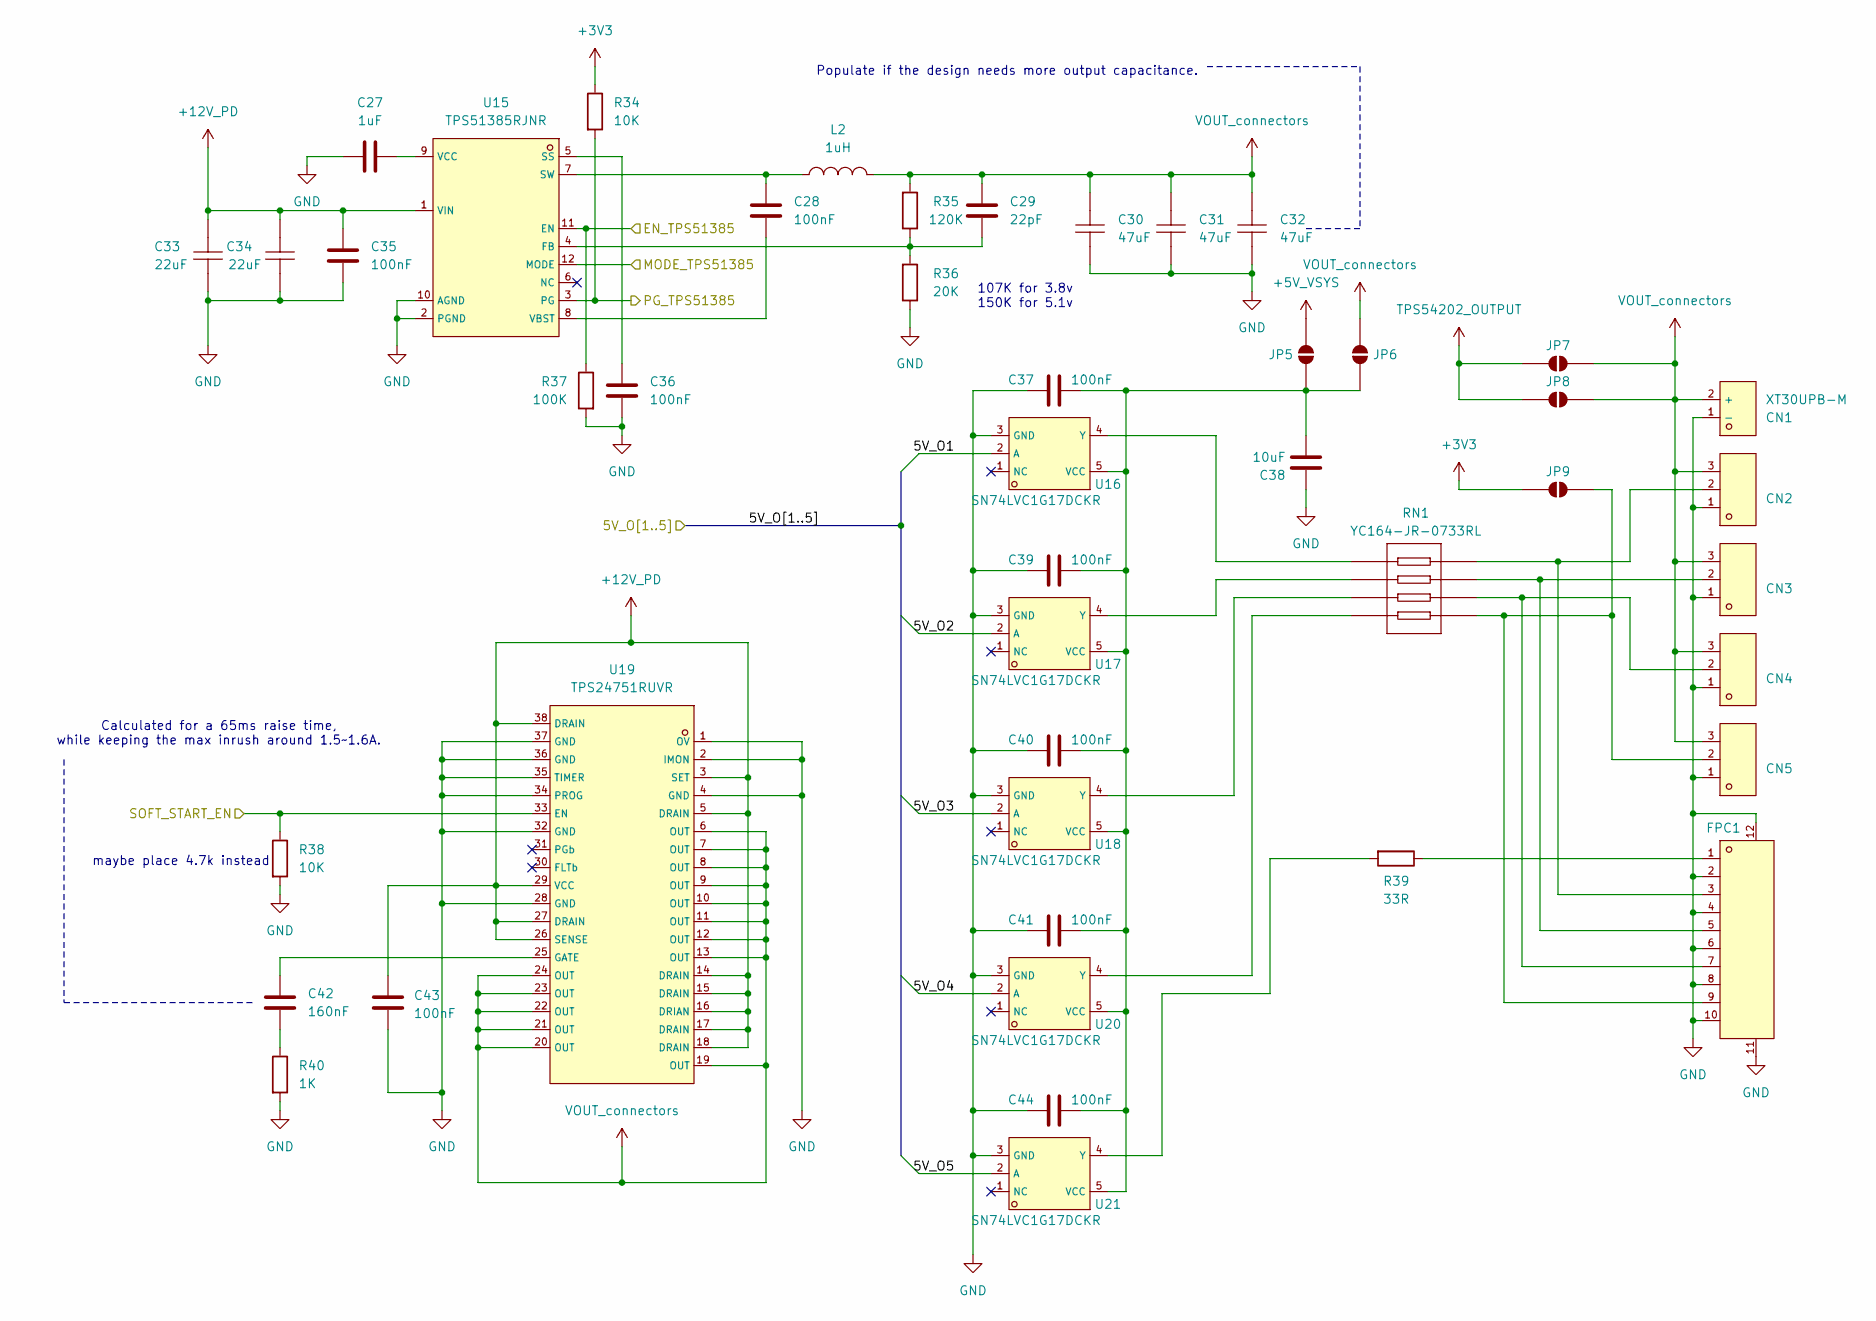
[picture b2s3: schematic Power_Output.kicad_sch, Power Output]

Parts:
C27: 1uF; C_0402_1005Metric_Pad0.74x0.62mm_HandSolder
C28, C35, C36, C37, C39, C40, C41, C43, C44: 100nF; C_0402_1005Metric_Pad0.74x0.62mm_HandSolder
C29: 22pF; C_0402_1005Metric_Pad0.74x0.62mm_HandSolder
C30, C31, C32: 47uF; C426659_C1206; LCSC C426659
C33, C34: 22uF; C778721_C1210; LCSC C778721
C38: 10uF; C_0805_2012Metric_Pad1.18x1.45mm_HandSolder
C42: 160nF; C_0402_1005Metric_Pad0.74x0.62mm_HandSolder
CN1: XT30UPB-M; C428721_CONN-TH_XT30UPB-M; LCSC C428721
CN2, CN3, CN4, CN5: B03B-XASK-1-A(LF)(SN); C264992_CONN-TH_B03B-XASK-1-A-LF-SN; LCSC C264992
FPC1: XW05202-100R-00; C2906114_FPC-SMD_10P-P0_50_HCTL_XW05202-100R-00; LCSC C2906114
JP5, JP6, JP7, JP8, JP9: SolderJumper_2_Open; SolderJumper-2_P1.3mm_Open_RoundedPad1.0x1.5mm
L2: 1uH; C845068_IND-SMD_L10_2-W10_2-LS10_8; LCSC C845068
R34, R38: 10K; R_0402_1005Metric_Pad0.72x0.64mm_HandSolder
R35: 120K; R_0402_1005Metric_Pad0.72x0.64mm_HandSolder
R36: 20K; R_0402_1005Metric_Pad0.72x0.64mm_HandSolder
R37: 100K; R_0402_1005Metric_Pad0.72x0.64mm_HandSolder
R39: 33R; R_0402_1005Metric_Pad0.72x0.64mm_HandSolder
R40: 1K; R_0402_1005Metric_Pad0.72x0.64mm_HandSolder
RN1: YC164-JR-0733RL; C165956_RES-ARRAY-SMD_0603-8P-L3_2-W1_6-BL; LCSC C165956
U15: TPS51385RJNR; C22418767_QFN-12_L3_0-W2_0-P0_5-TL_NB680; LCSC C22418767
U16, U17, U18, U20, U21: SN74LVC1G17DCKR; C10425_SC-70-5_L2_1-W1_3-P0_65-LS2_1-BR; LCSC C10425
U19: TPS24751RUVR; C2653596_VQFN-36_L7_0-W3_5-P0_50-BL-EP; LCSC C2653596

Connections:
+3V3: JP9.1 (A), R34.1; also elsewhere on the board
+5V_VSYS: JP5.2 (B); also elsewhere on the board
+12V_PD: C33.2, C34.2, C35.1, C43.1, U15.1 (VIN), U19.3 (SET), U19.5 (DRAIN), U19.14 (DRAIN), U19.15 (DRAIN), U19.16 (DRIAN), U19.17 (DRAIN), U19.18 (DRAIN), U19.26 (SENSE), U19.27 (DRAIN), U19.29 (VCC), U19.38 (DRAIN); also elsewhere on the board
/P01: U15.12 (MODE); also elsewhere on the board
/P02: R37.1, U15.11 (EN); also elsewhere on the board
/P03: R34.2, U15.3 (PG); also elsewhere on the board
/P04: R38.1, U19.33 (EN); also elsewhere on the board
/Power_Output/5V_O1: U16.2 (A); also elsewhere on the board
/Power_Output/5V_O2: U17.2 (A); also elsewhere on the board
/Power_Output/5V_O3: U18.2 (A); also elsewhere on the board
/Power_Output/5V_O4: U20.2 (A); also elsewhere on the board
/Power_Output/5V_O5: U21.2 (A); also elsewhere on the board
GND: C27.1, C30.1, C31.1, C32.1, C33.1, C34.1, C35.2, C36.1, C37.2, C38.2, C39.2, C40.2, C41.2, C43.2, C44.2, CN1.1 (-), CN2.1, CN3.1, CN4.1, CN5.1, FPC1.2, FPC1.4, FPC1.6, FPC1.8, FPC1.10, FPC1.11, FPC1.12, R36.1, R37.2, R38.2, R40.2, U15.2 (PGND), U15.10 (AGND), U16.3 (GND), U17.3 (GND), U18.3 (GND), U19.1 (OV), U19.2 (IMON), U19.4 (GND), U19.28 (GND), U19.32 (GND), U19.34 (PROG), U19.35 (TIMER), U19.36 (GND), U19.37 (GND), U20.3 (GND), U21.3 (GND); also elsewhere on the board
unnamed: C42.2, R40.1
unnamed: CN2.2, FPC1.3, RN1.8
unnamed: CN3.2, FPC1.5, RN1.7
unnamed: CN4.2, FPC1.7, RN1.6
unnamed: FPC1.1, R39.1
unnamed: C37.1, C38.1, C39.1, C40.1, C41.1, C44.1, JP5.1 (A), JP6.1 (A), U16.5 (VCC), U17.5 (VCC), U18.5 (VCC), U20.5 (VCC), U21.5 (VCC)
unnamed: CN5.2, FPC1.9, JP9.2 (B), RN1.5
unnamed: C29.2, R35.1, R36.2, U15.4 (FB)
unnamed: C36.2, U15.5 (SS)
unnamed: C28.1, L2.1, U15.7 (SW)
unnamed: C28.2, U15.8 (VBST)
unnamed: C27.2, U15.9 (VCC)
unnamed: RN1.1, U16.4 (Y)
unnamed: RN1.2, U17.4 (Y)
unnamed: RN1.3, U18.4 (Y)
unnamed: C42.1, U19.25 (GATE)
unnamed: RN1.4, U20.4 (Y)
unnamed: R39.2, U21.4 (Y)
TPS54202_OUTPUT: JP7.1 (A), JP8.1 (A); also elsewhere on the board
VOUT_connectors: C29.1, C30.2, C31.2, C32.2, CN1.2 (+), CN2.3, CN3.3, CN4.3, CN5.3, JP6.2 (B), JP7.2 (B), JP8.2 (B), L2.2, R35.2, U19.6 (OUT), U19.7 (OUT), U19.8 (OUT), U19.9 (OUT), U19.10 (OUT), U19.11 (OUT), U19.12 (OUT), U19.13 (OUT), U19.19 (OUT), U19.20 (OUT), U19.21 (OUT), U19.22 (OUT), U19.23 (OUT), U19.24 (OUT)

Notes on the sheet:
Populate if the design needs more output capacitance.
maybe place 4.7k instead
107K for 3.8v 150K for 5.1v
Calculated for a 65ms raise time, while keeping the max inrush around 1.5~1.6A.
